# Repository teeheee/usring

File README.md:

# Us Sensor Ring (short usring) 

These are all files needed to manufacture, use, modify and programm the sensoring.
More information can be found in "doku/usring-doku.pdf".

# Credit

* twi library from Martin Junghans
* uart library from Peter Fleury

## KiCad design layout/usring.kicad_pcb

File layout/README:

TODO:
	am multiplexer VEE->GND nicht VCC!!!
	sensor nummerierung überarbeiten
	10 poliger goldboard5 stecker

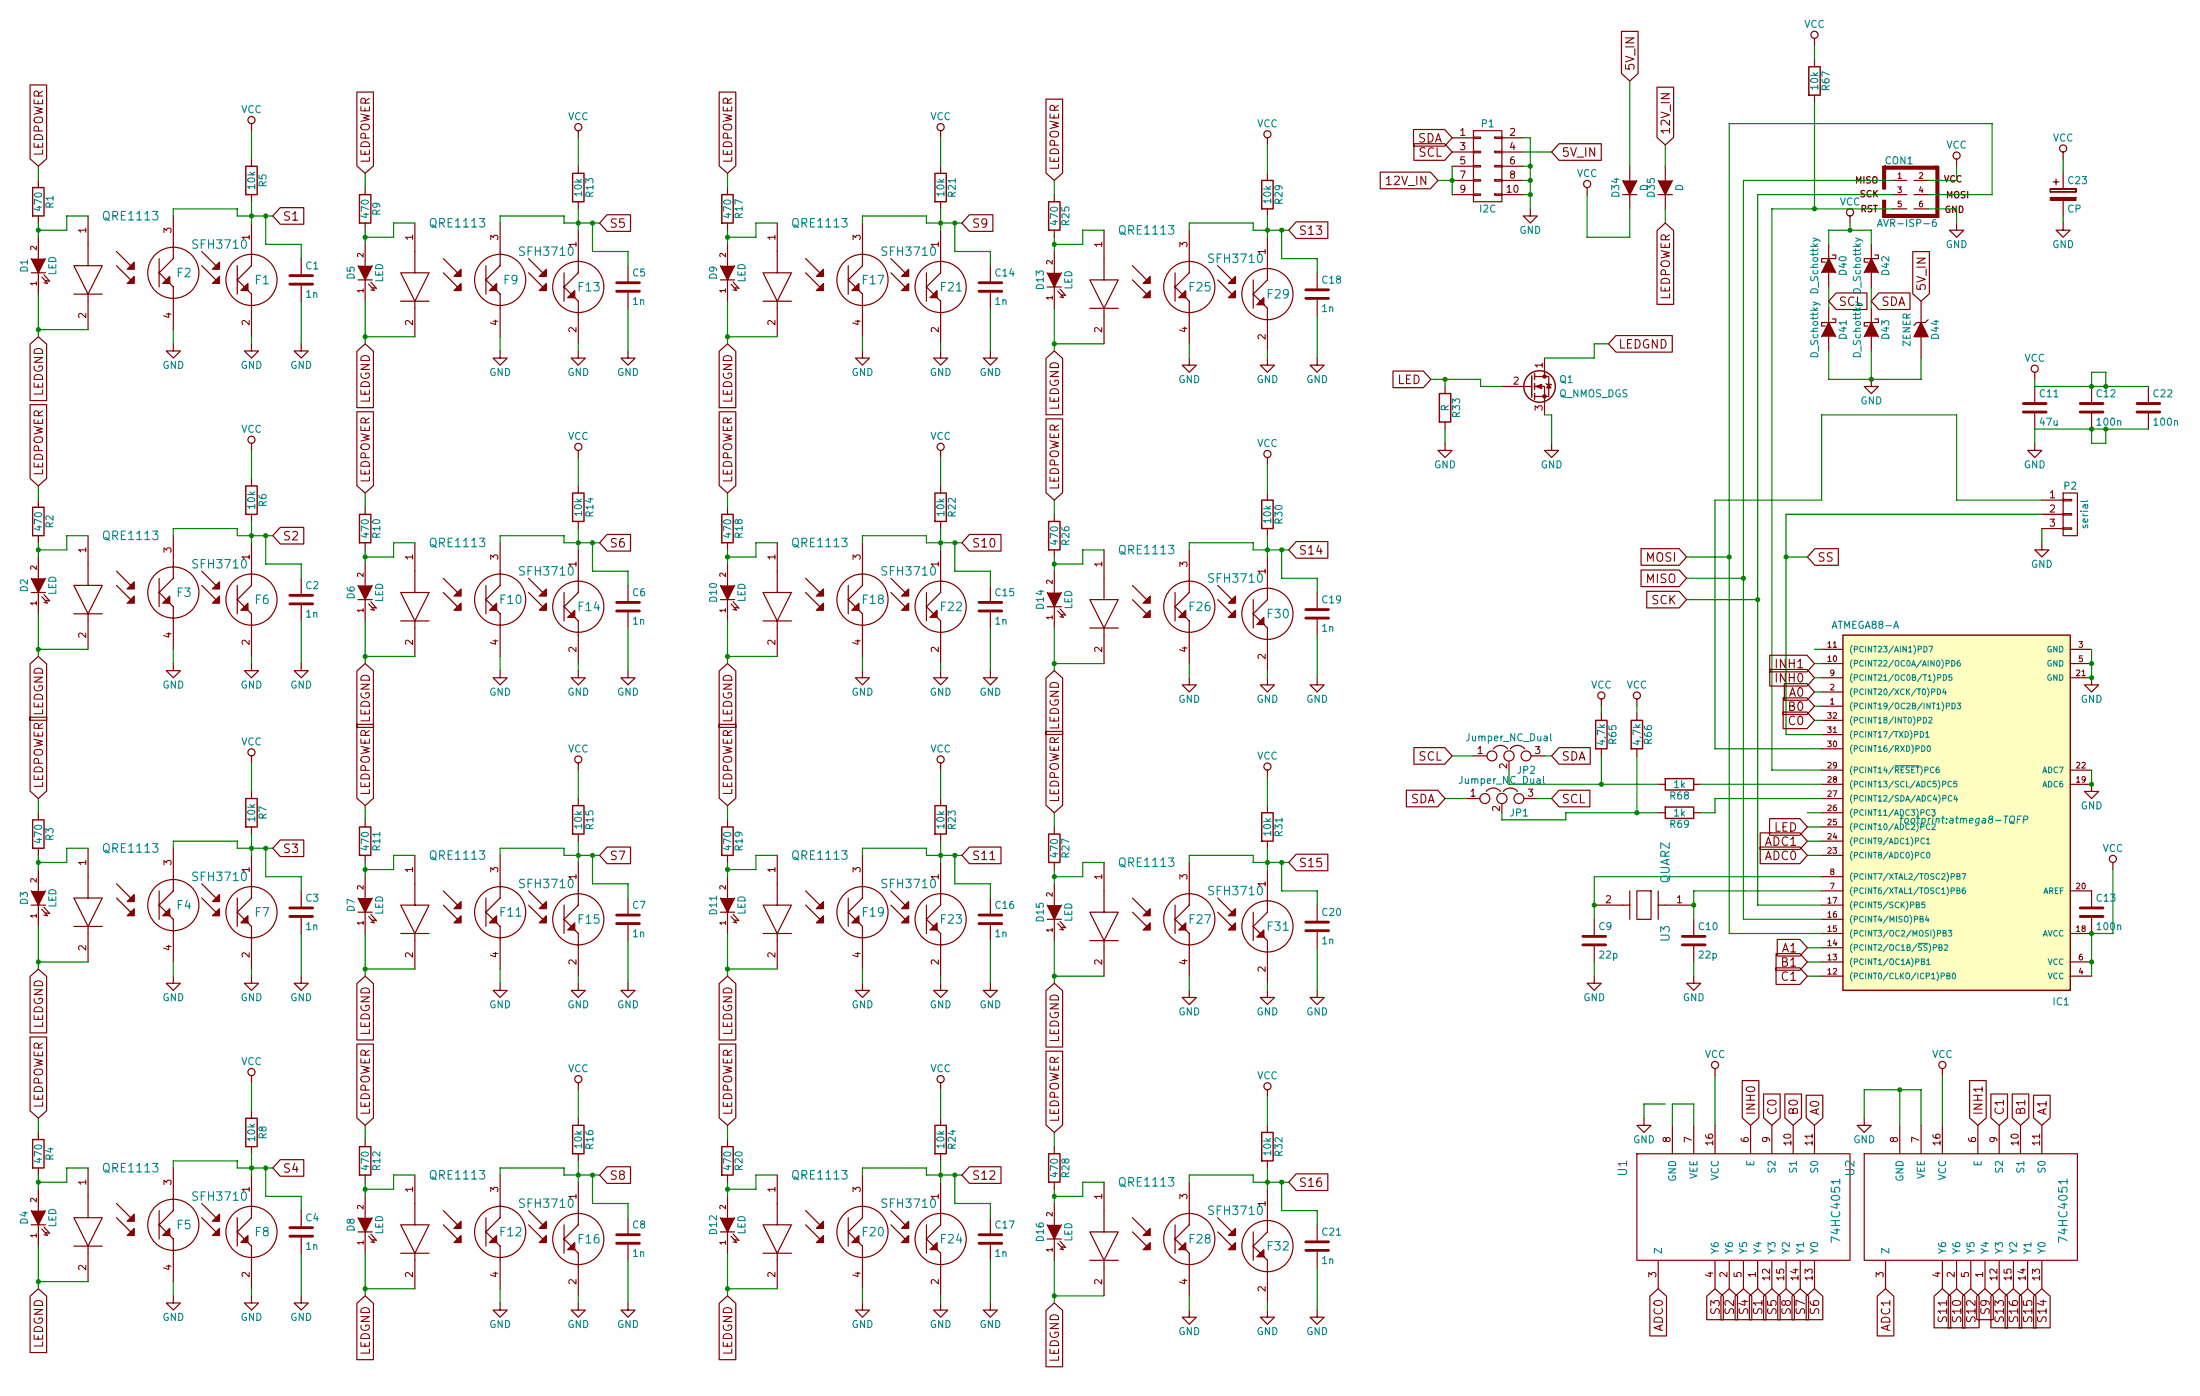
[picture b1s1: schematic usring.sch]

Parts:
C1, C2, C3, C4, C5, C6, C7, C8, C14, C15, C16, C17, C18, C19, C20, C21: 1n; C_0805
C9, C10: 22p; C_0805
C11: 47u; C_0805
C12, C13, C22: 100n; C_0805
C23: CP; CP_Radial_Tantal_D8.0mm_P2.50mm
CON1: AVR-ISP-6; AVR-ISP
D1, D2, D3, D4, D5, D6, D7, D8, D9, D10, D11, D12, D13, D14, D15, D16: LED; 1206_LED
D34, D35: D; Diode_throughole
D40, D41, D42, D43: D_Schottky; Shotkey-SOD-123
D44: ZENER; SMD-shotkey
F1, F6, F7, F8, F13, F14, F15, F16, F21, F22, F23, F24, F29, F30, F31, F32: SFH3710
F2, F3, F4, F5, F9, F10, F11, F12, F17, F18, F19, F20, F25, F26, F27, F28: QRE1113
IC1: ATMEGA88-A; atmega8-TQFP
JP1, JP2: Jumper_NC_Dual; GS3
P1: I2C; Pin_Header_Straight_2x05
P2: serial; PINHEAD1-3
Q1: Q_NMOS_DGS; SOT23
R1, R2, R3, R4, R9, R10, R11, R12, R17, R18, R19, R20, R25, R26, R27, R28: 470; R_0805
R5, R6, R7, R8, R13, R14, R15, R16, R21, R22, R23, R24, R29, R30, R31, R32, R67: 10k; R_0805
R33: R; R_0805
R65, R66: 4,7k; R_0805
R68, R69: 1k; R_0805
U1, U2: 74HC4051; 74HC4051-SO16
U3: QUARZ; QUARZ-HC49

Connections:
5V_IN: D34.2 (A), D44.1 (K), P1.4
12V_IN: D35.2 (A), P1.5, P1.7, P1.9
A0: IC1.2 ((PCINT20/XCK/T0)PD4), U1.11 (S0)
A1: IC1.14 ((PCINT2/OC1B/~SS~)PB2), U2.11 (S0)
ADC0: IC1.23 ((PCINT8/ADC0)PC0), U1.3 (Z)
ADC1: IC1.24 ((PCINT9/ADC1)PC1), U2.3 (Z)
B0: IC1.1 ((PCINT19/OC2B/INT1)PD3), U1.10 (S1)
B1: IC1.13 ((PCINT1/OC1A)PB1), U2.10 (S1)
C0: IC1.32 ((PCINT18/INT0)PD2), U1.9 (S2)
C1: IC1.12 ((PCINT0/CLKO/ICP1)PB0), U2.9 (S2)
INH0: IC1.9 ((PCINT21/OC0B/T1)PD5), U1.6 (E)
INH1: IC1.10 ((PCINT22/OC0A/AIN0)PD6), U2.6 (E)
LED: IC1.25 ((PCINT10/ADC2)PC2), Q1.2 (G), R33.1
LEDGND: D1.1 (K), D2.1 (K), D3.1 (K), D4.1 (K), D5.1 (K), D6.1 (K), D7.1 (K), D8.1 (K), D9.1 (K), D10.1 (K), D11.1 (K), D12.1 (K), D13.1 (K), D14.1 (K), D15.1 (K), D16.1 (K), F2.2, F3.2, F4.2, F5.2, F9.2, F10.2, F11.2, F12.2, F17.2, F18.2, F19.2, F20.2, F25.2, F26.2, F27.2, F28.2, Q1.1 (D)
LEDPOWER: D35.1 (K), R1.1, R2.1, R3.1, R4.1, R9.1, R10.1, R11.1, R12.1, R17.1, R18.1, R19.1, R20.1, R25.1, R26.1, R27.1, R28.1
MISO: CON1.1, IC1.16 ((PCINT4/MISO)PB4)
MOSI: CON1.4, IC1.15 ((PCINT3/OC2/MOSI)PB3)
unnamed: C9.1, IC1.8 ((PCINT7/XTAL2/TOSC2)PB7), U3.2
unnamed: C10.1, IC1.7 ((PCINT6/XTAL1/TOSC1)PB6), U3.1
unnamed: C13.1, IC1.20 (AREF)
unnamed: CON1.5, IC1.29 ((PCINT14/~RESET~)PC6), R67.2
unnamed: D1.2 (A), F2.1, R1.2
unnamed: D2.2 (A), F3.1, R2.2
unnamed: D3.2 (A), F4.1, R3.2
unnamed: D4.2 (A), F5.1, R4.2
unnamed: D5.2 (A), F9.1, R9.2
unnamed: D6.2 (A), F10.1, R10.2
unnamed: D7.2 (A), F11.1, R11.2
unnamed: D8.2 (A), F12.1, R12.2
unnamed: D9.2 (A), F17.1, R17.2
unnamed: D10.2 (A), F18.1, R18.2
unnamed: D11.2 (A), F19.1, R19.2
unnamed: D12.2 (A), F20.1, R20.2
unnamed: D13.2 (A), F25.1, R25.2
unnamed: D14.2 (A), F26.1, R26.2
unnamed: D15.2 (A), F27.1, R27.2
unnamed: D16.2 (A), F28.1, R28.2
unnamed: IC1.27 ((PCINT12/SDA/ADC4)PC4), R69.1
unnamed: IC1.28 ((PCINT13/SCL/ADC5)PC5), R68.1
unnamed: IC1.30 ((PCINT16/RXD)PD0), P2.1
unnamed: JP1.2, R66.2, R69.2
unnamed: JP2.2, R65.2, R68.2
S1: C1.1, F1.1, F2.3, R5.2, U1.1 (Y4)
S2: C2.1, F3.3, F6.1, R6.2, U1.2 (Y6)
S3: C3.1, F4.3, F7.1, R7.2, U1.4 (Y6)
S4: C4.1, F5.3, F8.1, R8.2, U1.5 (Y5)
S5: C5.1, F9.3, F13.1, R13.2, U1.12 (Y3)
S6: C6.1, F10.3, F14.1, R14.2, U1.13 (Y0)
S7: C7.1, F11.3, F15.1, R15.2, U1.14 (Y1)
S8: C8.1, F12.3, F16.1, R16.2, U1.15 (Y2)
S9: C14.1, F17.3, F21.1, R21.2, U2.1 (Y4)
S10: C15.1, F18.3, F22.1, R22.2, U2.2 (Y6)
S11: C16.1, F19.3, F23.1, R23.2, U2.4 (Y6)
S12: C17.1, F20.3, F24.1, R24.2, U2.5 (Y5)
S13: C18.1, F25.3, F29.1, R29.2, U2.12 (Y3)
S14: C19.1, F26.3, F30.1, R30.2, U2.13 (Y0)
S15: C20.1, F27.3, F31.1, R31.2, U2.14 (Y1)
S16: C21.1, F28.3, F32.1, R32.2, U2.15 (Y2)
SCK: CON1.3, IC1.17 ((PCINT5/SCK)PB5)
SCL: D40.2 (A), D41.1 (K), JP1.3, JP2.1, P1.3
SDA: D42.2 (A), D43.1 (K), JP1.1, JP2.3, P1.1
SS: IC1.31 ((PCINT17/TXD)PD1), P2.2
VCC: C11.1, C12.1, C13.2, C22.1, C23.1, CON1.2, D34.1 (K), D40.1 (K), D42.1 (K), IC1.4 (VCC), IC1.6 (VCC), IC1.18 (AVCC), R5.1, R6.1, R7.1, R8.1, R13.1, R14.1, R15.1, R16.1, R21.1, R22.1, R23.1, R24.1, R29.1, R30.1, R31.1, R32.1, R65.1, R66.1, R67.1, U1.16 (VCC), U2.16 (VCC)

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
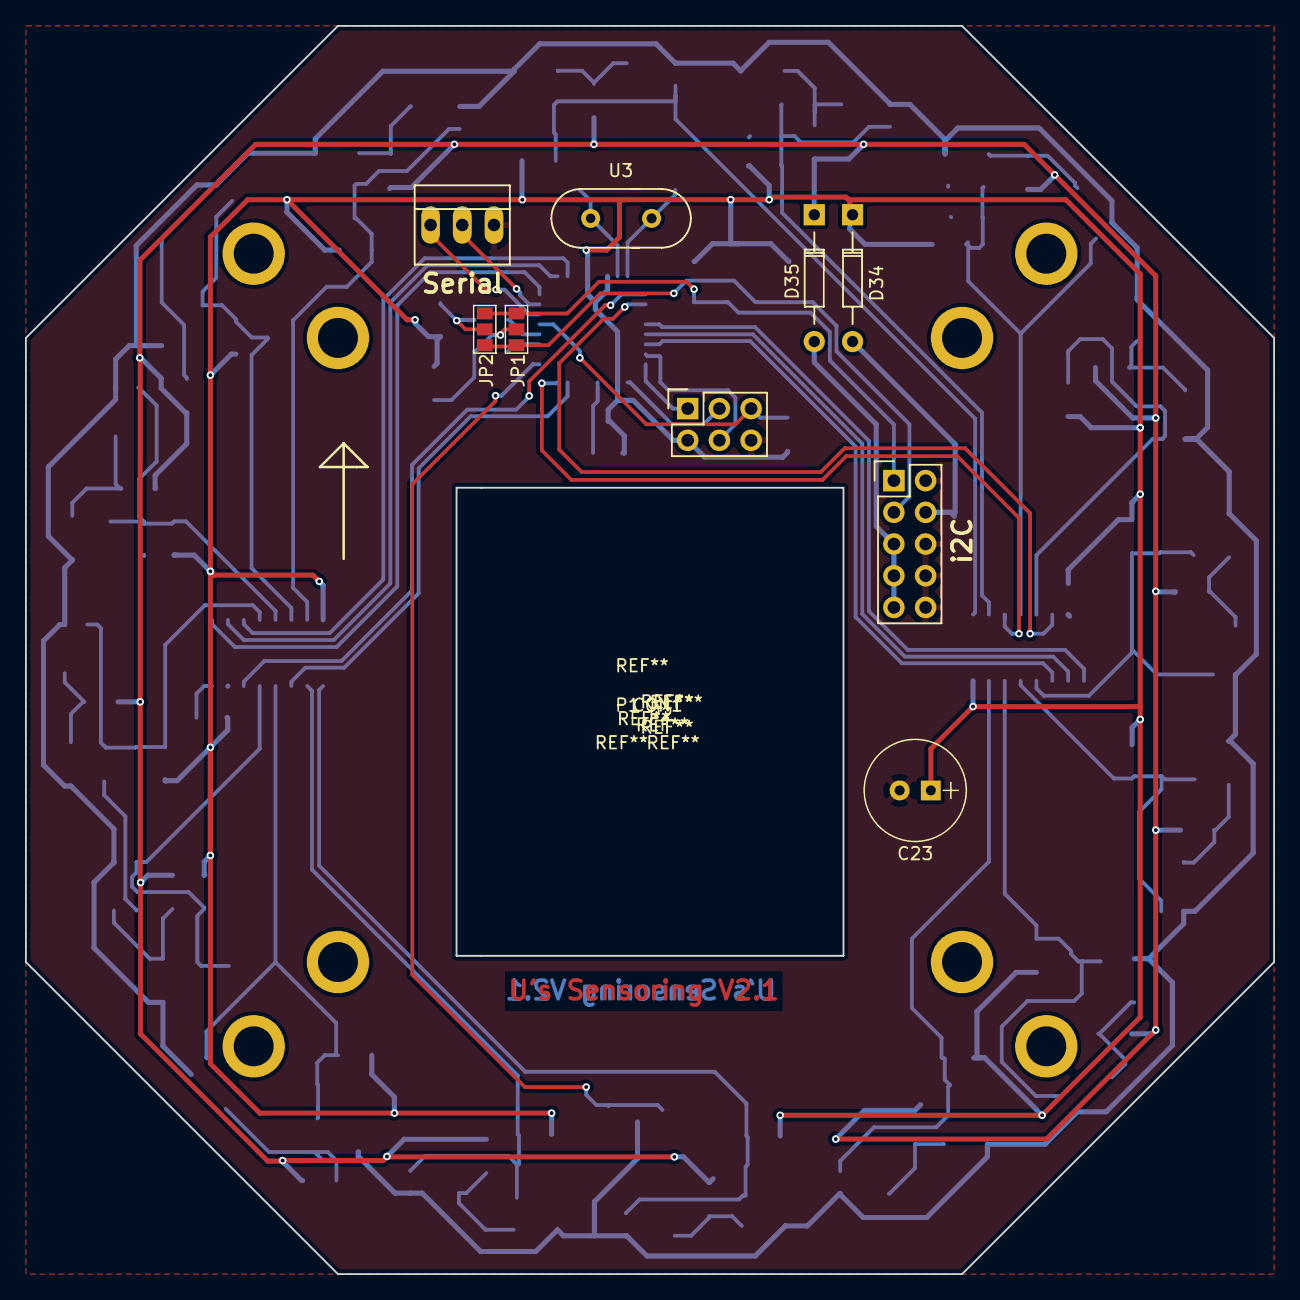
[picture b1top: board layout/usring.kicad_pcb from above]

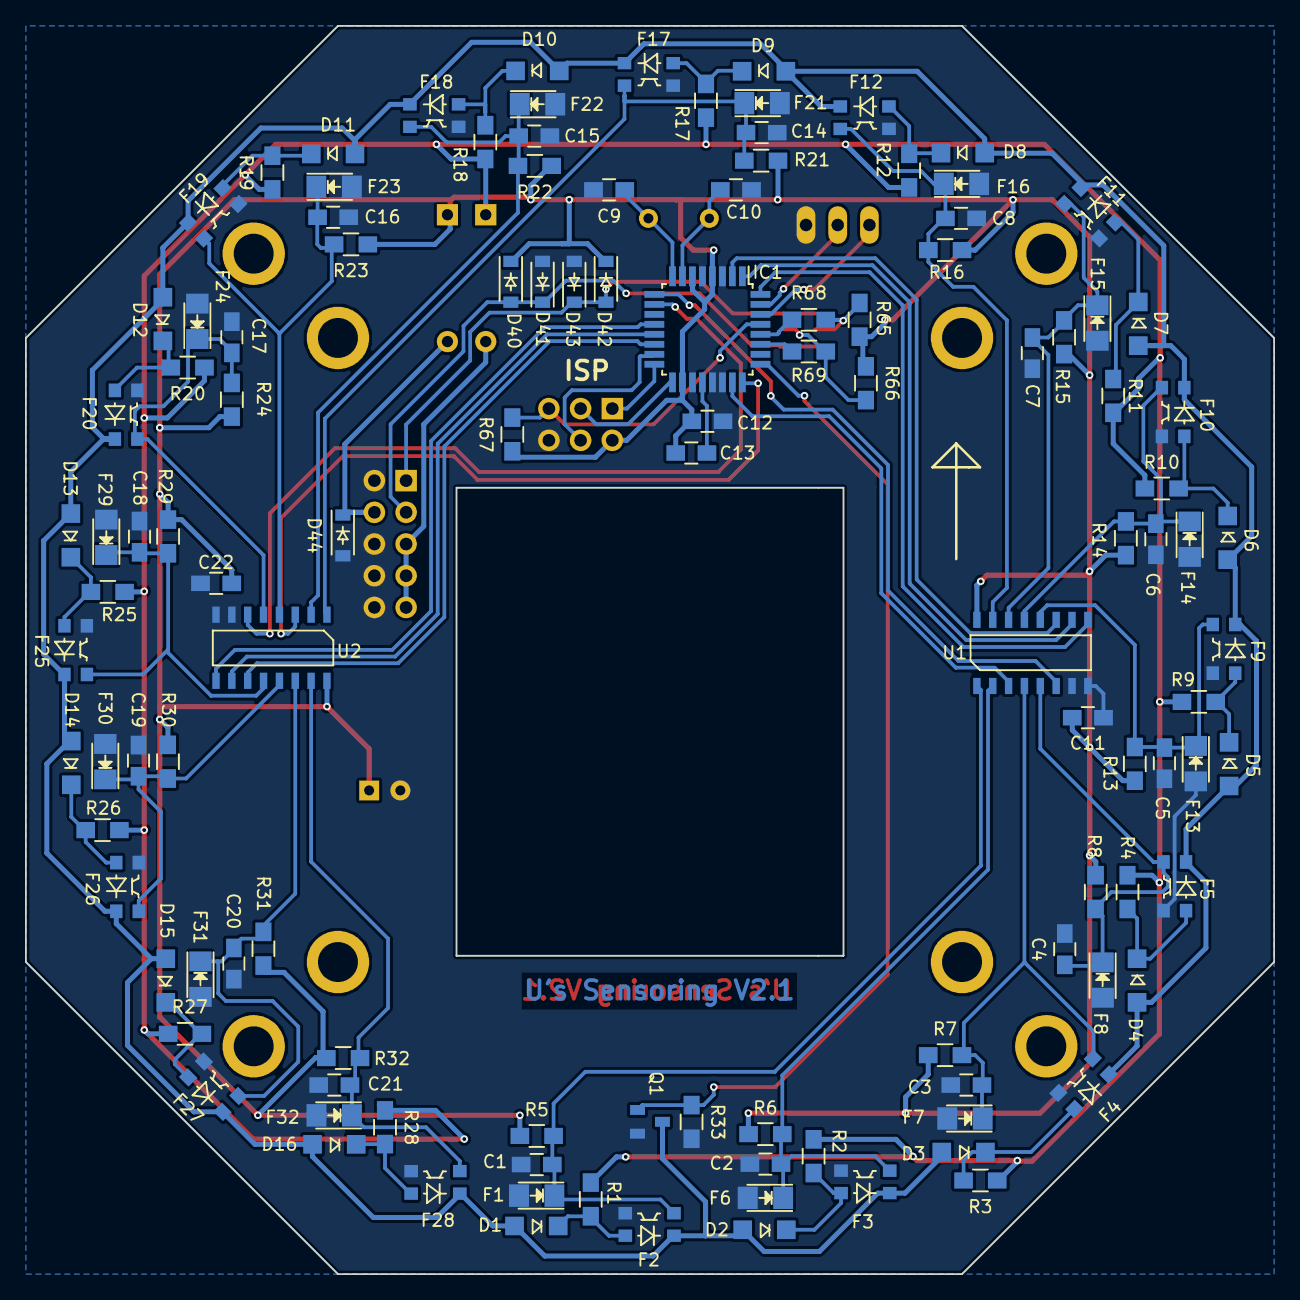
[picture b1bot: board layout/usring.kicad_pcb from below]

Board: 2 copper layers, 100.0 x 100.0 mm, 126 parts (117 on the bottom side), 64 nets.

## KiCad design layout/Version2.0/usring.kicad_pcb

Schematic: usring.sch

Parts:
BB1: ADNS9800; adns9800
C1, C2, C3, C4, C5, C6, C7, C8, C12, C13, C15, C17, C19, C21: 100n; C_0805_HandSoldering
C9, C10: 22p; C_0805_HandSoldering
C11: 47u; C_Radial_D5_L6_P2.5
C14: 470p; C_0805_HandSoldering
C16, C18, C20, C22, C23, C24: 1u; C_0805_HandSoldering
CON1: AVR-ISP-6; Pin_Header_Straight_2x03
D1, D2, D3, D4, D5, D6, D7, D8, D9, D10, D11, D12, D13, D14, D15, D16, D17, D18, D19, D20, D21, D22, D23, D24, D25, D26, D27, D28, D29, D30, D31, D32: LED; LED_1206
D34, D35: D; Diode_DO-35_SOD27_Horizontal_RM10
D36, D37, D38, D39, D40, D41, D42, D43: D_Schottky; SOD-123
D44: ZENER; SOD-80
F1, F2, F3, F4, F5, F6, F7, F8, F9, F10, F11, F12, F13, F14, F15, F16: SFH3710; LED_PLCC_2835_Handsoldering
IC1: ATMEGA88-A; TQFP-32_7x7mm_Pitch0.8mm
JP1, JP2, JP3: Jumper_NO_Small; C_0603_HandSoldering
P1: I2C; Pin_Header_Straight_2x05
P2: serial; PINHEAD1-3
Q1: Q_PMOS_GSD; SOT-416
R1, R2, R3, R4, R17, R18, R19, R20, R33, R34, R35, R36, R49, R50, R51, R52: 470; R_0805_HandSoldering
R5, R6, R7, R8, R21, R22, R23, R24, R37, R38, R39, R40, R53, R54, R55, R56, R67: 10k; R_0805_HandSoldering
R9, R10, R11, R12, R25, R26, R27, R28, R41, R42, R43, R44, R57, R58, R59, R60: 330; R_0805_HandSoldering
R13, R14, R15, R16, R29, R30, R31, R32, R45, R46, R47, R48, R61, R62, R63, R64, R68, R69: 1k; R_0805_HandSoldering
R65, R66: 4,7k; R_0805_HandSoldering
R70, R72, R74: 1,8k; R_0805_HandSoldering
R71, R73, R75: 3,3k; R_0805_HandSoldering
R76: 0; R_0805_HandSoldering
RV1, RV2, RV3, RV4: 10k; Potentiometer_Bourns_3296P_3-8Zoll_Angular_ScrewFront
U1, U2, U3, U4: LM339; SOIC-14_3.9x8.7mm_Pitch1.27mm
U5: APE8865N-33-HF-3; SOT-23
X1: QUARTZCMS4; Crystal_HC49-U_Vertical

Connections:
5V_IN: D44.1 (K), P1.4, R76.1
12V_IN: D35.2 (A), P1.5, P1.7, P1.9
/+5V: C2.1, C4.1, C6.1, C8.1, C11.1, C12.1, C13.2, C23.1, CON1.2, D34.1 (K), D40.1 (K), D42.1 (K), IC1.4 (VCC), IC1.6 (VCC), IC1.18 (AVCC), R5.1, R6.1, R7.1, R8.1, R9.1, R10.1, R11.1, R12.1, R21.1, R22.1, R23.1, R24.1, R25.1, R26.1, R27.1, R28.1, R37.1, R38.1, R39.1, R40.1, R41.1, R42.1, R43.1, R44.1, R53.1, R54.1, R55.1, R56.1, R57.1, R58.1, R59.1, R60.1, R65.1, R66.1, R67.1, RV1.3, RV2.3, RV3.3, RV4.3, U1.3 (V+), U2.3 (V+), U3.3 (V+), U4.3 (V+), U5.3 (VIN)
CS_3V: BB1.3 (CS), R74.2, R75.1
DGND: BB1.14 (DGND), C21.2, C22.2
LEDPOWER: D35.1 (K), R1.1, R2.1, R3.1, R4.1, R17.1, R18.1, R19.1, R20.1, R33.1, R34.1, R35.1, R36.1, R49.1, R50.1, R51.1, R52.1
MISO: BB1.4 (MISO), CON1.1, D38.2 (A), D39.1 (K), IC1.16 ((PCINT4/MISO)PB4), R13.1
MOSI: CON1.4, IC1.15 ((PCINT3/OC2/MOSI)PB3), R14.1, R70.1
MOSI_3V: BB1.6 (MOSI), R70.2, R71.1
MOTION: BB1.7 (MOTION), D36.2 (A), D37.1 (K)
unnamed: BB1.1 (+VCSEL), C14.1, Q1.3 (D)
unnamed: BB1.2 (LASER_NEN), Q1.1 (G)
unnamed: BB1.8 (XY_LASER), BB1.16 (-VCSEL), C14.2
unnamed: C9.1, IC1.8 ((PCINT7/XTAL2/TOSC2)PB7), X1.1
unnamed: C10.1, IC1.7 ((PCINT6/XTAL1/TOSC1)PB6), X1.2 (3)
unnamed: C13.1, IC1.20 (AREF)
unnamed: CON1.5, IC1.29 ((PCINT14/~RESET~)PC6), R67.2
unnamed: D1.2 (A), R1.2
unnamed: D2.2 (A), R2.2
unnamed: D3.2 (A), R3.2
unnamed: D4.2 (A), R4.2
unnamed: D5.1 (K), R13.2, U1.2
unnamed: D5.2 (A), R9.2
unnamed: D6.1 (K), R14.2, U1.1
unnamed: D6.2 (A), R10.2
unnamed: D7.1 (K), R15.2, U1.13
unnamed: D7.2 (A), R11.2
unnamed: D8.1 (K), R16.2, U1.14
unnamed: D8.2 (A), R12.2
unnamed: D9.2 (A), R17.2
unnamed: D10.2 (A), R18.2
unnamed: D11.2 (A), R19.2
unnamed: D12.2 (A), R20.2
unnamed: D13.1 (K), R29.2, U2.2
unnamed: D13.2 (A), R25.2
unnamed: D14.1 (K), R30.2, U2.1
unnamed: D14.2 (A), R26.2
unnamed: D15.1 (K), R31.2, U2.13
unnamed: D15.2 (A), R27.2
unnamed: D16.1 (K), R32.2, U2.14
unnamed: D16.2 (A), R28.2
unnamed: D17.2 (A), R33.2
unnamed: D18.2 (A), R34.2
unnamed: D19.2 (A), R35.2
unnamed: D20.2 (A), R36.2
unnamed: D21.1 (K), R45.2, U3.2
unnamed: D21.2 (A), R41.2
unnamed: D22.1 (K), R46.2, U3.1
unnamed: D22.2 (A), R42.2
unnamed: D23.1 (K), R47.2, U3.13
unnamed: D23.2 (A), R43.2
unnamed: D24.1 (K), R48.2, U3.14
unnamed: D24.2 (A), R44.2
unnamed: D25.2 (A), R49.2
unnamed: D26.2 (A), R50.2
unnamed: D27.2 (A), R51.2
unnamed: D28.2 (A), R52.2
unnamed: D29.1 (K), R61.2, U4.2
unnamed: D29.2 (A), R57.2
unnamed: D30.1 (K), R62.2, U4.1
unnamed: D30.2 (A), R58.2
unnamed: D31.1 (K), R63.2, U4.13
unnamed: D31.2 (A), R59.2
unnamed: D32.1 (K), R64.2, U4.14
unnamed: D32.2 (A), R60.2
unnamed: D34.2 (A), R76.2
unnamed: F1.1, R5.2, U1.4 (-)
unnamed: F2.1, R6.2, U1.6 (-)
unnamed: F3.1, R7.2, U1.10 (-)
unnamed: F4.1, R8.2, U1.8 (-)
unnamed: F5.1, R21.2, U2.4 (-)
unnamed: F6.1, R22.2, U2.6 (-)
unnamed: F7.1, R23.2, U2.10 (-)
unnamed: F8.1, R24.2, U2.8 (-)
unnamed: F9.1, R37.2, U3.4 (-)
unnamed: F10.1, R38.2, U3.6 (-)
unnamed: F11.1, R39.2, U3.10 (-)
unnamed: F12.1, R40.2, U3.8 (-)
unnamed: F13.1, R53.2, U4.4 (-)
unnamed: F14.1, R54.2, U4.6 (-)
unnamed: F15.1, R55.2, U4.10 (-)
unnamed: F16.1, R56.2, U4.8 (-)
unnamed: IC1.27 ((PCINT12/SDA/ADC4)PC4), R69.1
unnamed: IC1.28 ((PCINT13/SCL/ADC5)PC5), R68.1
unnamed: IC1.30 ((PCINT16/RXD)PD0), P2.1
REF1: C1.1, JP1.1, RV1.2, U1.5 (+), U1.7 (+), U1.9 (+), U1.11 (+)
REF2: C3.1, JP2.2, JP3.1, RV2.2, U2.5 (+), U2.7 (+), U2.9 (+), U2.11 (+)
REF3: C5.1, JP3.2, RV3.2, U3.5 (+), U3.7 (+), U3.9 (+), U3.11 (+)
REF4: C7.1, JP1.2, JP2.1, RV4.2, U4.5 (+), U4.7 (+), U4.9 (+), U4.11 (+)
REFA: BB1.13 (REF1,8), C21.1, C22.1
SCK: CON1.3, IC1.17 ((PCINT5/SCK)PB5), R15.1, R72.1
SCK_3V: BB1.5 (SCK), R72.2, R73.1
SCL: D40.2 (A), D41.1 (K), P1.1, R65.2, R68.2
SDA: D42.2 (A), D43.1 (K), P1.3, R66.2, R69.2
SENS1: IC1.11 ((PCINT23/AIN1)PD7), R62.1
SENS2: IC1.10 ((PCINT22/OC0A/AIN0)PD6), R32.1
SENS3: IC1.9 ((PCINT21/OC0B/T1)PD5), R31.1
SENS4: IC1.2 ((PCINT20/XCK/T0)PD4), R29.1
SENS5: IC1.1 ((PCINT19/OC2B/INT1)PD3), R30.1
SENS6: IC1.32 ((PCINT18/INT0)PD2), R48.1
SENS9: IC1.26 ((PCINT11/ADC3)PC3), R47.1
SENS10: IC1.25 ((PCINT10/ADC2)PC2), R45.1
SENS11: IC1.24 ((PCINT9/ADC1)PC1), R46.1
SENS12: IC1.23 ((PCINT8/ADC0)PC0), R16.1
SENS13: IC1.14 ((PCINT2/OC1B/~SS~)PB2), R64.1
SENS14: IC1.13 ((PCINT1/OC1A)PB1), R63.1
SENS15: IC1.12 ((PCINT0/CLKO/ICP1)PB0), R61.1
VREG: BB1.9 (VDD5/3), BB1.10 (POWER_OPT), BB1.12 (REF3,3/VDD3,3), BB1.15 (VDDIO), C15.1, C16.1, C17.1, C18.1, C19.1, C20.1, C24.1, D36.1 (K), D38.1 (K), Q1.2 (S), U5.2 (VOUT)

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
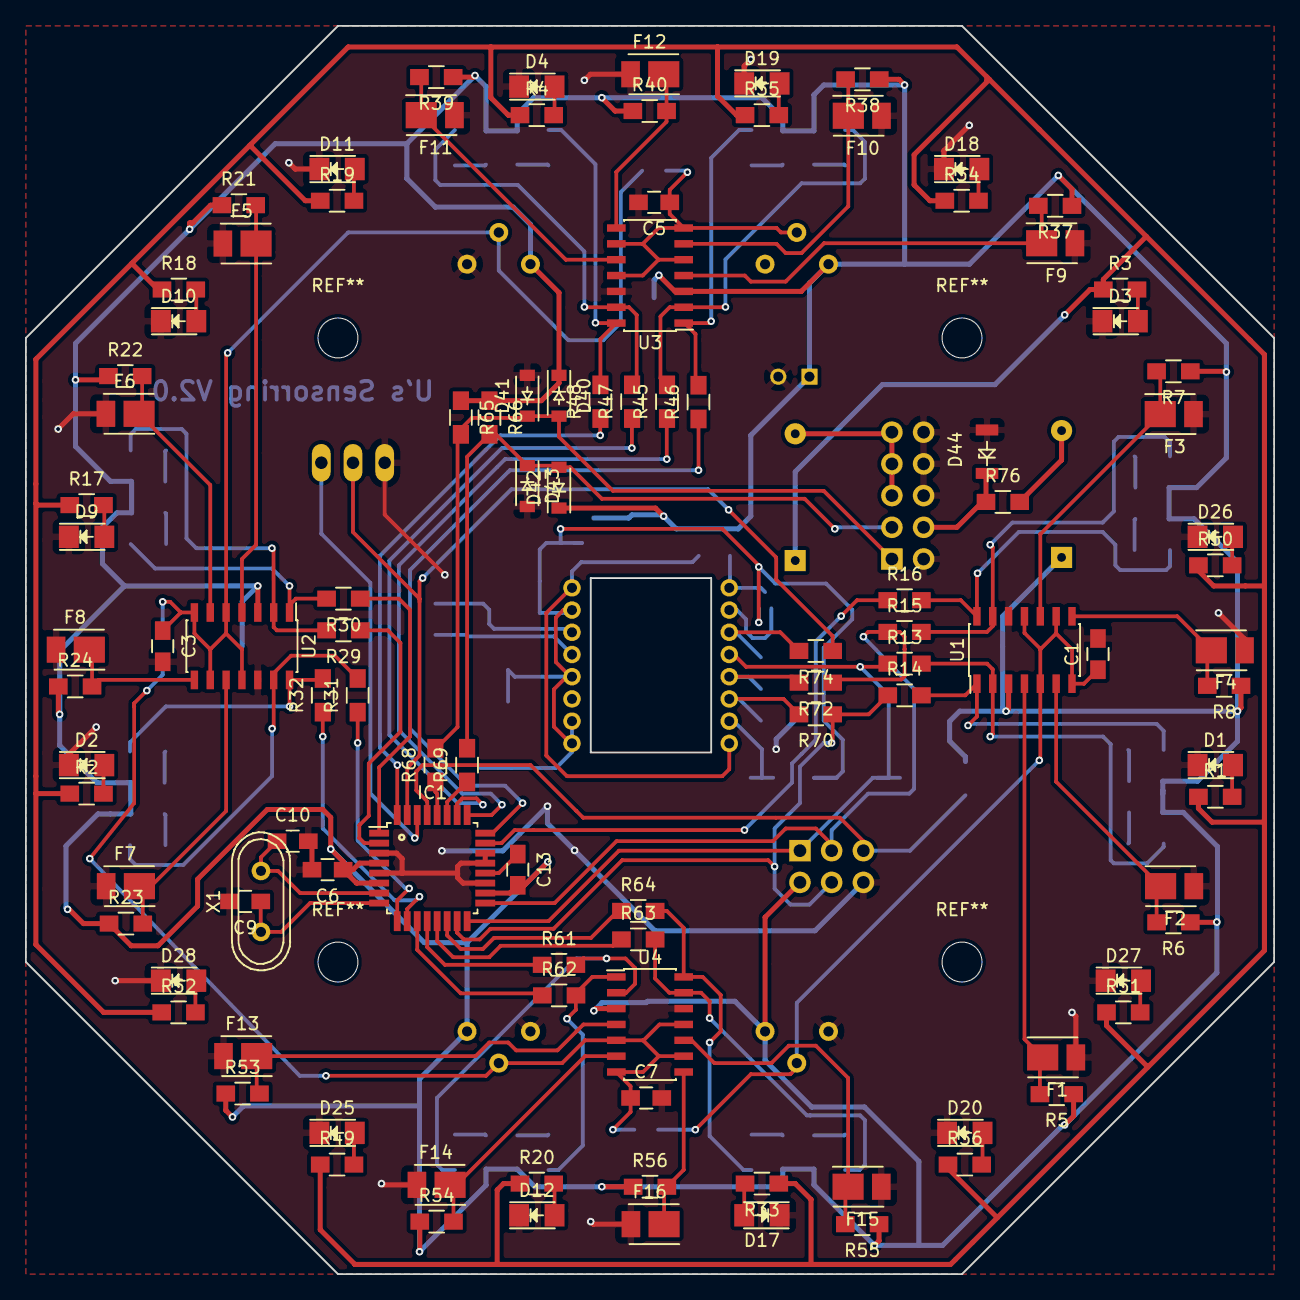
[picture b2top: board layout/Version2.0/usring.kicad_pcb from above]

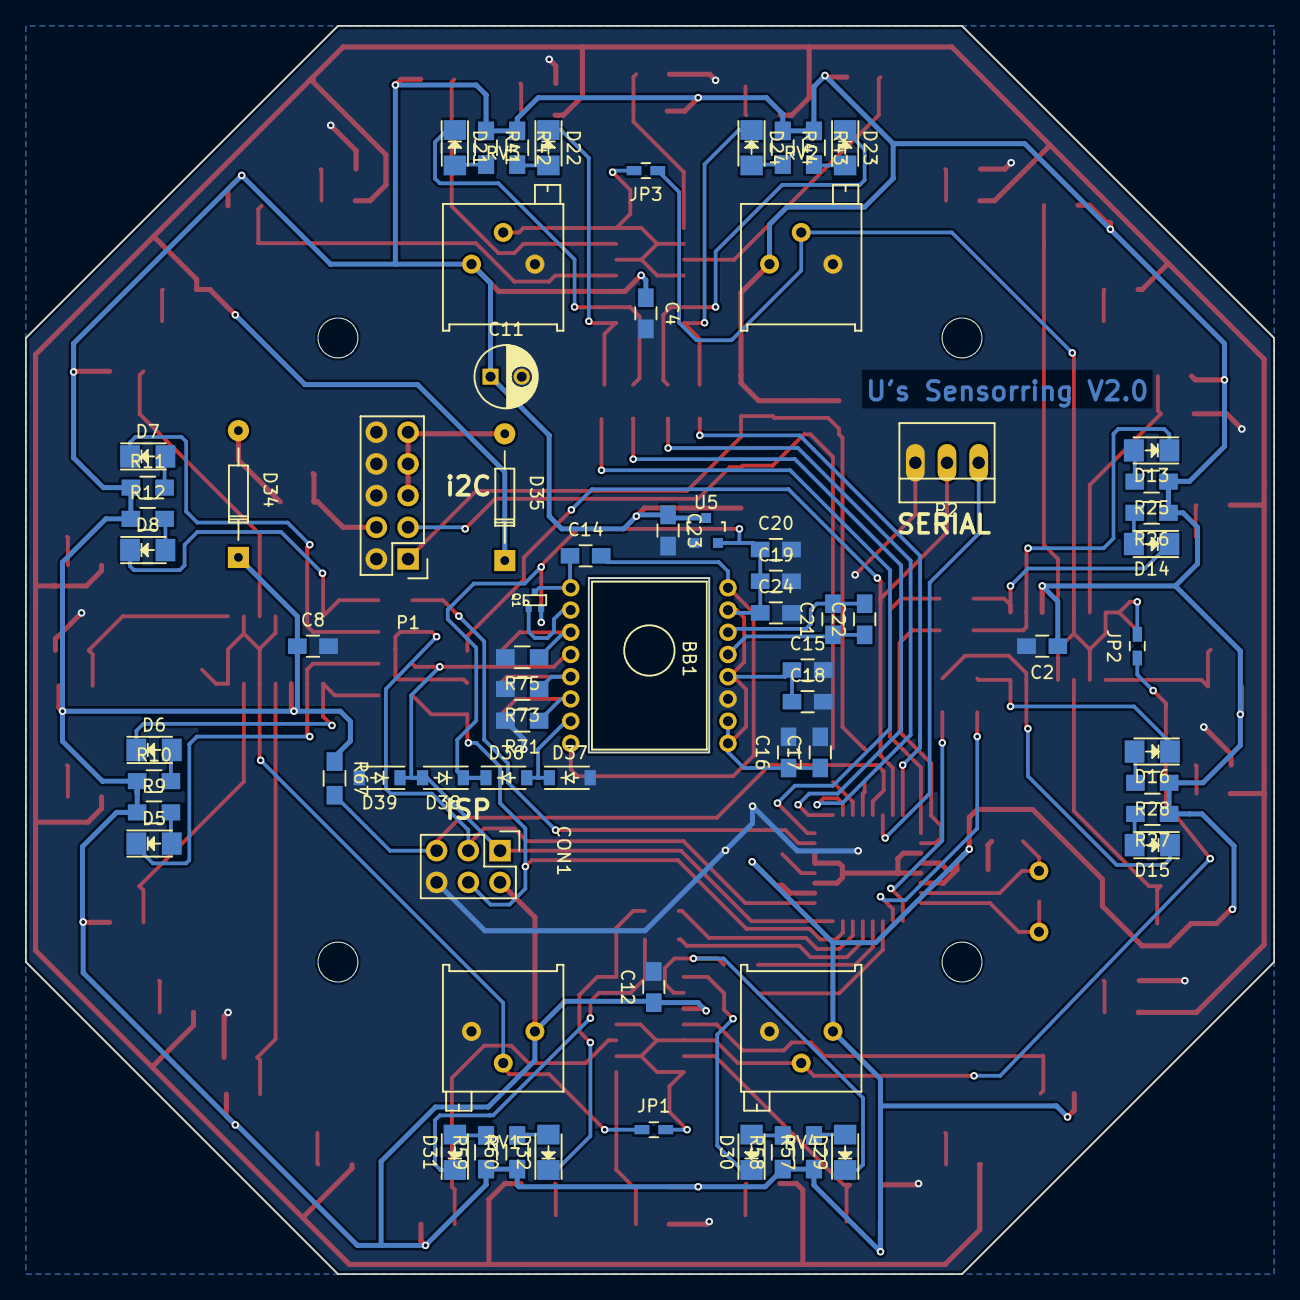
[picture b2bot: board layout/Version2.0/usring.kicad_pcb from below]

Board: 2 copper layers, 100.0 x 100.0 mm, 178 parts (71 on the bottom side), 110 nets.

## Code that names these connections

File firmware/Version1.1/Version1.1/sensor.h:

/*
 * sensor.h
 *
 * Created: 05.02.2016 20:01:00
 *  Author: alexander
 */ 


#ifndef SENSOR_H_
#define SENSOR_H_


#include <avr/io.h>

#define SENSOR_COUNT 16

#define DDR_S0		DDRD
#define PORT_S0		PORTD
#define PIN_S0		PIND
#define S0			PD2

#define DDR_S1		DDRC
#define PORT_S1		PORTC
#define PIN_S1		PINC
#define S1			PC3

#define DDR_S2		DDRD
#define PORT_S2		PORTD
#define PIN_S2		PIND
#define S2			PD4

#define DDR_S3		DDRD
#define PORT_S3		PORTD
#define PIN_S3		PIND
#define S3			PD3

#define DDR_S4		DDRD
#define PORT_S4		PORTD
#define PIN_S4		PIND
#define S4			PD6

#define DDR_S5		DDRD
#define PORT_S5		PORTD
#define PIN_S5		PIND
#define S5			PD5

#define DDR_S6		DDRB
#define PORT_S6		PORTB
#define PIN_S6		PINB
#define S6			PB0

#define DDR_S7		DDRD
#define PORT_S7		PORTD
#define PIN_S7		PIND
#define S7			PD7

#define DDR_S8		DDRB
#define PORT_S8		PORTB
#define PIN_S8		PINB
#define S8			PB2

#define DDR_S9		DDRB
#define PORT_S9		PORTB
#define PIN_S9		PINB
#define S9			PB1

#define DDR_S10		DDRB
#define PORT_S10	PORTB
#define PIN_S10		PINB
#define S10			PB4

#define DDR_S11		DDRB
#define PORT_S11	PORTB
#define PIN_S11		PINB
#define S11			PB3

#define DDR_S12		DDRC
#define PORT_S12	PORTC
#define PIN_S12		PINC
#define S12			PC0

#define DDR_S13		DDRB
#define PORT_S13	PORTB
#define PIN_S13		PINB
#define S13			PB5

#define DDR_S14		DDRC
#define PORT_S14	PORTC
#define PIN_S14		PINC
#define S14			PC2

#define DDR_S15		DDRC
#define PORT_S15	PORTC
#define PIN_S15		PINC
#define S15			PC1

void init_sensors();

uint8_t* get_value_array();

uint16_t get_value_bit();



#endif /* SENSOR_H_ */

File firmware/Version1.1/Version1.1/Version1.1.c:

/*
 * Version1.c
 *
 * Created: 05.02.2016 19:38:33
 *  Author: alexander
 */ 




#define DEBUG

#include <avr/io.h>
#include <avr/interrupt.h>
#include <util/delay.h>

#ifdef DEBUG
	#include <stdio.h>
#endif

#include "twislave.h"
#include "uart.h"
#include "sensor.h"
#include "processing.h"


#define BAUD 9600UL      // Baudrate


void init()
{
	cli();
	init_twi_slave(66);			
	uart_init(UART_BAUD_SELECT(BAUD,F_CPU));
	DDRD|=(1<<PD1);
	DDRD&=~((1<<PD0)|(1<<PD4)|(1<<PD5));
	init_sensors();
	sei();	
}

void process()
{
	uint16_t val = get_value_bit();
	txbuffer[0]=val>>8;
	txbuffer[1]=val&0xff00;
	
	
	
	uint8_t* dat = get_value_array();
	
	struct blockinfo info[SENSOR_COUNT];
	
	uint8_t block_count = find_blocks(dat,SENSOR_COUNT,info);

	static uint8_t last_direction = 0;
	static uint8_t last_distance = 0;
	static uint8_t start_direction = 0;
	static uint8_t start_distance = 0;
	uint8_t direction = 0;
	uint8_t distance = 0;

	static uint8_t online_flag = 0;

	if(block_count==0)//no line
	{
		online_flag=0;
		distance = 0;
		direction = 0;
	}
	else // line
	{
		if(block_count==1) // einfach weil nur ein block
		{
			direction = info[0].block_middle;
			distance = SENSOR_COUNT-info[0].block_size; // realy???
		}
		if(block_count>=2) // zwei bloecke muessen verbunden werden oder?
		{
			uint8_t l = (info[0].block_middle-info[1].block_middle+SENSOR_COUNT)%SENSOR_COUNT;
			uint8_t r = (info[1].block_middle-info[0].block_middle+SENSOR_COUNT)%SENSOR_COUNT;
			if(l>r)
			{
				distance = SENSOR_COUNT - r;
				direction = info[0].block_middle + r/2;
			}
			else
			{
				distance = SENSOR_COUNT - l;
				direction = info[1].block_middle + l/2;
			}
		}	
		if(online_flag==0)
		{
			start_direction = direction;
			start_distance = distance;
		}
		online_flag = 1;
		last_direction=direction;
		last_distance=distance;
	}

	txbuffer[3]=start_direction;
	txbuffer[4]=start_distance;
	txbuffer[5]=direction;
	txbuffer[6]=distance;
	txbuffer[7]=last_direction;
	txbuffer[8]=last_distance;

	#ifdef DEBUG
	static uint16_t delaycounter = 0;
	delaycounter++;
	if(delaycounter==1000)
	{
	delaycounter=0;
	char buffer[100];
	uart_putc(0x1b);
	uart_puts("[2J");
	uart_putc(0x1b);
	uart_puts("[H");
	sprintf(buffer,"block_count: %d\r\n",block_count);uart_puts(buffer);
	sprintf(buffer,"start_direction: %d\r\n",start_direction);uart_puts(buffer);
	sprintf(buffer,"start_distance: %d\r\n",start_distance);uart_puts(buffer);
	sprintf(buffer,"direction: %d\r\n",direction);uart_puts(buffer);
	sprintf(buffer,"distance: %d\r\n",distance);uart_puts(buffer);
	sprintf(buffer,"last_direction: %d\r\n",last_direction);uart_puts(buffer);
	sprintf(buffer,"last_distance: %d\r\n",last_distance);uart_puts(buffer);
	uart_puts("data: ");
	for (int x = 0; x < SENSOR_COUNT;x++)
	{
		if(x%4==0)
			uart_putc('|');
		if(dat[x])
			uart_putc('1');
		else
			uart_putc('0');
	}
	uart_puts("                  \r\n");
	sprintf(buffer,"\t\t15:%d 0:%d 1:%d\r\n",dat[15],dat[0],dat[1]);uart_puts(buffer);
	sprintf(buffer,"\t14:%d\t\t\t2:%d\r\n",dat[14],dat[2]);uart_puts(buffer);
	sprintf(buffer,"13:%d\t\t\t\t\t3:%d\r\n",dat[13],dat[3]);uart_puts(buffer);
	sprintf(buffer,"12:%d\t\t\t\t\t4:%d\r\n",dat[12],dat[4]);uart_puts(buffer);
	sprintf(buffer,"11:%d\t\t\t\t\t5:%d\r\n",dat[11],dat[5]);uart_puts(buffer);
	sprintf(buffer,"\t10:%d\t\t\t6:%d\r\n",dat[10],dat[6]);uart_puts(buffer);
	sprintf(buffer,"\t\t9:%d 8:%d 7:%d\r\n",dat[9],dat[8],dat[7]);uart_puts(buffer);
		
	}
	
	#endif
}
/*			1

	3				4


			2
*/
int main(void)
{
	init();
	
	while(1)
    {
        process();
	}
}

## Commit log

2017-03-05 README.md created online with Bitbucket
2017-03-12 platine in fertigung
2017-11-26 new firmware version. still needs testing
2018-03-07 cleanup and doku
2018-03-07 as7 template added
2018-09-05 major bug fixes
2018-11-23 fixed buffer overflow issue
2018-11-23 better calibration
2018-12-21 added stencil
2018-12-21 new features (filter, single threshold)
2018-12-21 bugfix
2019-04-26 optimierte Firmware Version
2019-04-26 new template
2019-05-03 made more stable version
